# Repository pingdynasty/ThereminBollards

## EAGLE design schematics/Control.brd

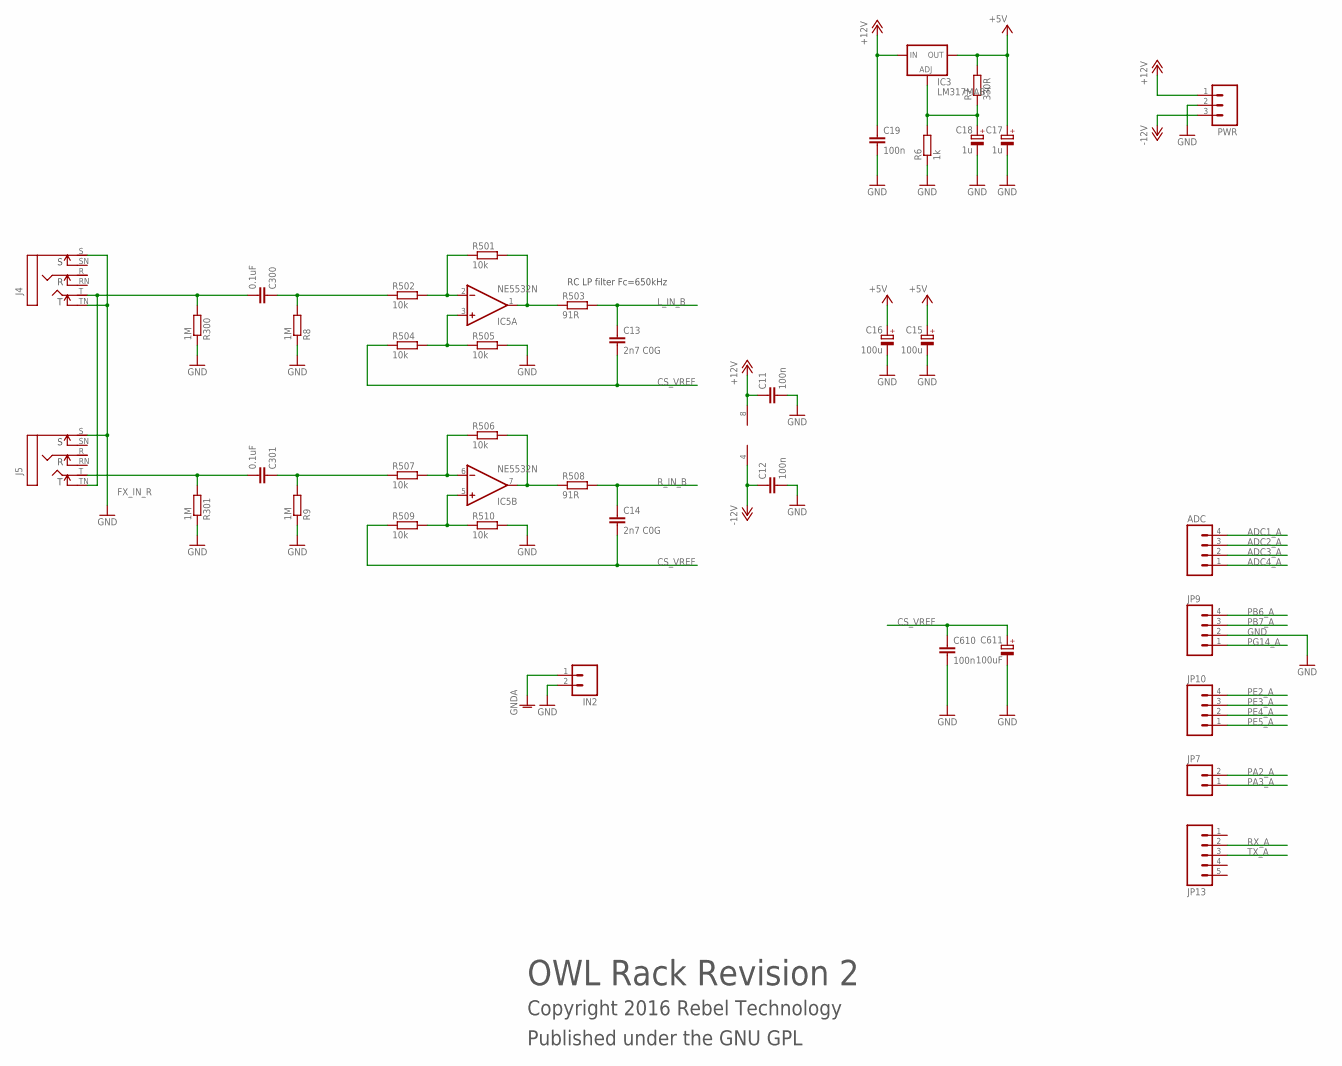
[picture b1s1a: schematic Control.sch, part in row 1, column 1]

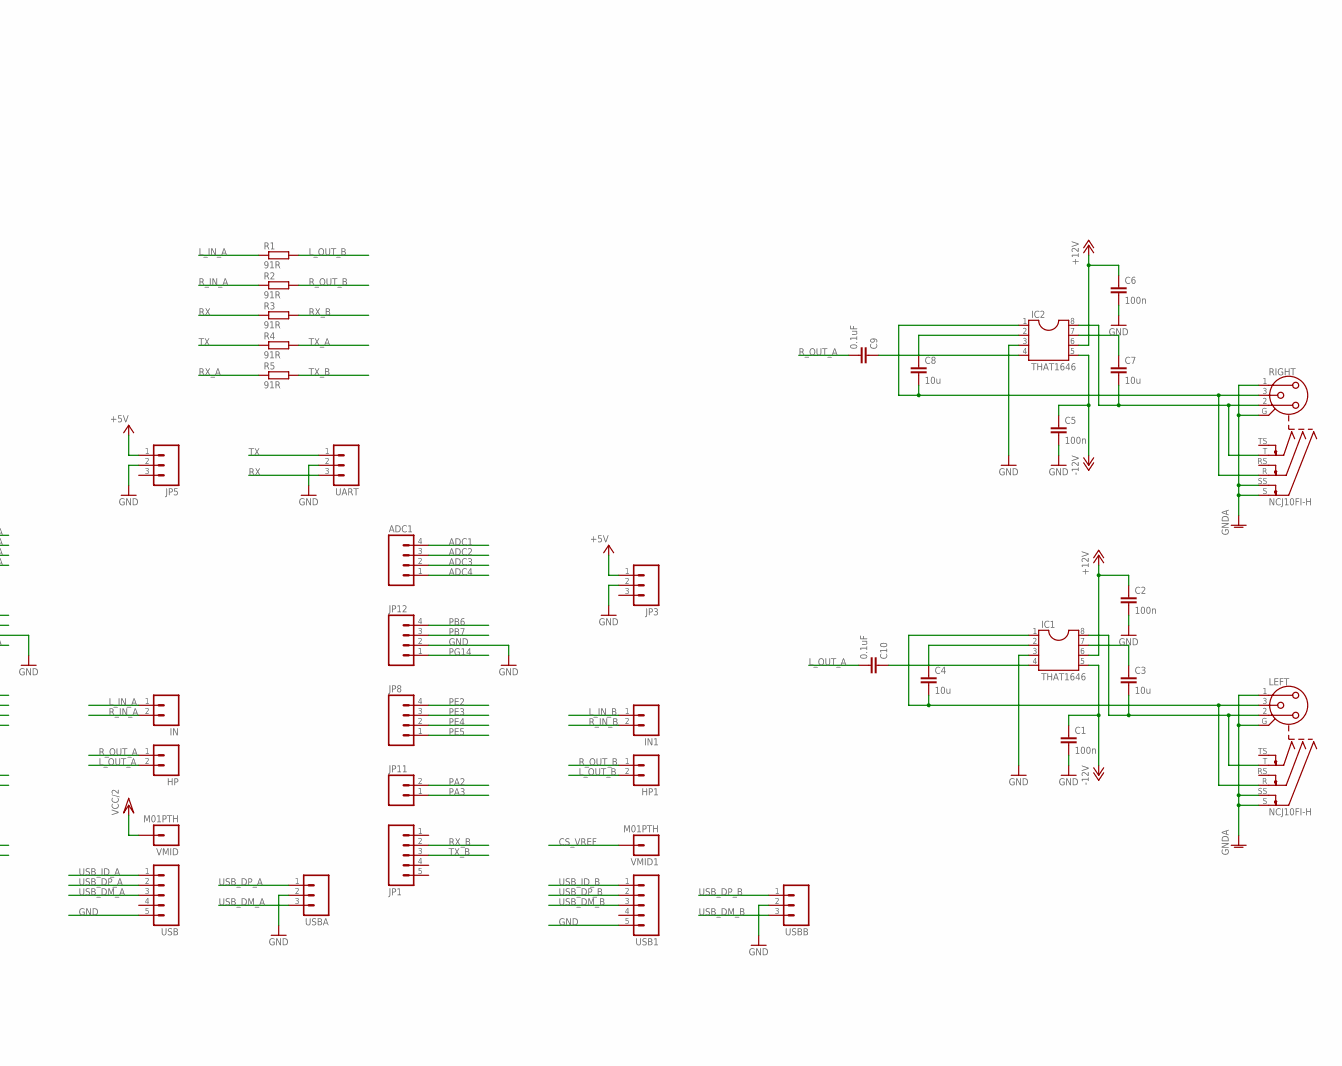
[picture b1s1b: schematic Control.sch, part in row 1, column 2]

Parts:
ADC, ADC1: M04PTH; 1X04
C1, C2, C5, C6, C11, C12, C19, C610: 100n; C050-025X075
C3, C4, C7, C8: 10u; C050-025X075
C9, C10, C300, C301: 0.1uF; C5B3.5
C13, C14: 2n7 C0G; C050-025X075
C15, C16: 100u; E2,5-7
C17, C18: 1u; E2,5-7
C611: 100uF; E2,5-7
HP, HP1: M02PTH; 1X02
IC1, IC2: THAT1646; DIL08
IC3: LM317MABT; TO220L1
IC5: NE5532N; DIL08
IN, IN1, IN2: M02PTH; 1X02
J4, J5: NEUTRIK_NMJ6HCD2; NMJ6HCD2
JP1, JP13: M05PTH; 1X05
JP3, JP5: M03PTH; 1X03
JP7, JP11: M02PTH; 1X02
JP8, JP9, JP10, JP12: M04PTH; 1X04
LEFT: NCJ10FI-H
PWR: M03PTH; 1X03
R1, R2, R3, R4, R5, R503, R508: 91R; 0204/7
R6: 1k; 0204/7
R7: 330R; 0204/7
R8, R9, R300, R301: 1M; 0204/7
R501, R502, R504, R505, R506, R507, R509, R510: 10k; 0204/7
RIGHT: NCJ10FI-H
UART: M03PTH; 1X03
USB, USB1: M05PTH; 1X05
USBA: M03PTH; 1X03
USBB: M03PTH; 1X03
VMID, VMID1: M01PTH; 1X01

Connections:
+5V: C15.+, C16.+, C17.+, IC3.2 (OUT), JP3.1, JP5.1, R7.2
+12V: C2.1, C6.1, C11.1, C19.1, IC1.6, IC2.6, IC3.3 (IN), IC5.8 (V+), PWR.1
-12V: C1.1, C5.1, C12.1, IC1.5, IC2.5, IC5.4 (V-), PWR.3
ADC1: ADC1.4
ADC1_A: ADC.4
ADC2: ADC1.3
ADC2_A: ADC.3
ADC3: ADC1.2
ADC3_A: ADC.2
ADC4: ADC1.1
ADC4_A: ADC.1
CS_VREF: C13.2, C14.2, C610.1, C611.+, R504.1, R509.1, VMID1.1
FX_IN_L: C300.2, J4.T, J5.TN, R300.2
FX_IN_R: C301.2, J5.T, R301.2
GND: C1.2, C2.2, C5.2, C6.2, C11.2, C12.2, C15.-, C16.-, C17.-, C18.-, C19.2, C610.2, C611.-, IC1.3, IC2.3, IN2.2, J4.S, J4.TN, J5.S, JP3.2, JP5.2, JP9.2, JP12.2, PWR.2, R6.1, R8.1, R9.1, R300.1, R301.1, R505.2, R510.2, UART.2, USB.5, USB1.5, USBA.2, USBB.2
GNDA: IN2.1, LEFT.1, LEFT.G, LEFT.S, LEFT.SS, RIGHT.1, RIGHT.G, RIGHT.S, RIGHT.SS
L_IN_A: IN.1, R1.1
L_IN_B: C13.1, IN1.1, R503.2
L_OUT_A: C10.2, HP.2
L_OUT_B: HP1.2, R1.2
unnamed: IC5.7 (OUT), R506.2, R508.1
unnamed: C3.2, IC1.8, LEFT.2, LEFT.T
unnamed: C4.2, IC1.1, LEFT.3, LEFT.R
unnamed: C3.1, IC1.7
unnamed: C4.1, IC1.2
unnamed: C9.1, IC2.4
unnamed: C7.1, IC2.7
unnamed: C10.1, IC1.4
unnamed: C8.1, IC2.2
unnamed: C18.+, IC3.1 (ADJ), R6.2, R7.1
unnamed: C7.2, IC2.8, RIGHT.2, RIGHT.T
unnamed: C8.2, IC2.1, RIGHT.3, RIGHT.R
unnamed: C300.1, R8.2, R502.1
unnamed: C301.1, R9.2, R507.1
unnamed: IC5.3 (+IN), R504.2, R505.1
unnamed: IC5.2 (-IN), R501.1, R502.2
unnamed: IC5.1 (OUT), R501.2, R503.1
unnamed: IC5.5 (+IN), R509.2, R510.1
unnamed: IC5.6 (-IN), R506.1, R507.2
PA2: JP11.2
PA2_A: JP7.2
PA3: JP11.1
PA3_A: JP7.1
PB6: JP12.4
PB6_A: JP9.4
PB7: JP12.3
PB7_A: JP9.3
PE2: JP8.4
PE2_A: JP10.4
PE3: JP8.3
PE3_A: JP10.3
PE4: JP8.2
PE4_A: JP10.2
PE5: JP8.1
PE5_A: JP10.1
PG14: JP12.1
PG14_A: JP9.1
RX: R3.1, UART.3
RX_A: JP13.2, R5.1
RX_B: JP1.2, R3.2
R_IN_A: IN.2, R2.1
R_IN_B: C14.1, IN1.2, R508.2
R_OUT_A: C9.2, HP.1
R_OUT_B: HP1.1, R2.2
TX: R4.1, UART.1
TX_A: JP13.3, R4.2
TX_B: JP1.3, R5.2
USB_DM_A: USB.3, USBA.3
USB_DM_B: USB1.3, USBB.3
USB_DP_A: USB.2, USBA.1
USB_DP_B: USB1.2, USBB.1
USB_ID_A: USB.1
USB_ID_B: USB1.1
VCC/2: VMID.1

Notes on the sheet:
OWL Rack Revision 2
Copyright 2016 Rebel Technology
Published under the GNU GPL
RC LP filter Fc=650kHz

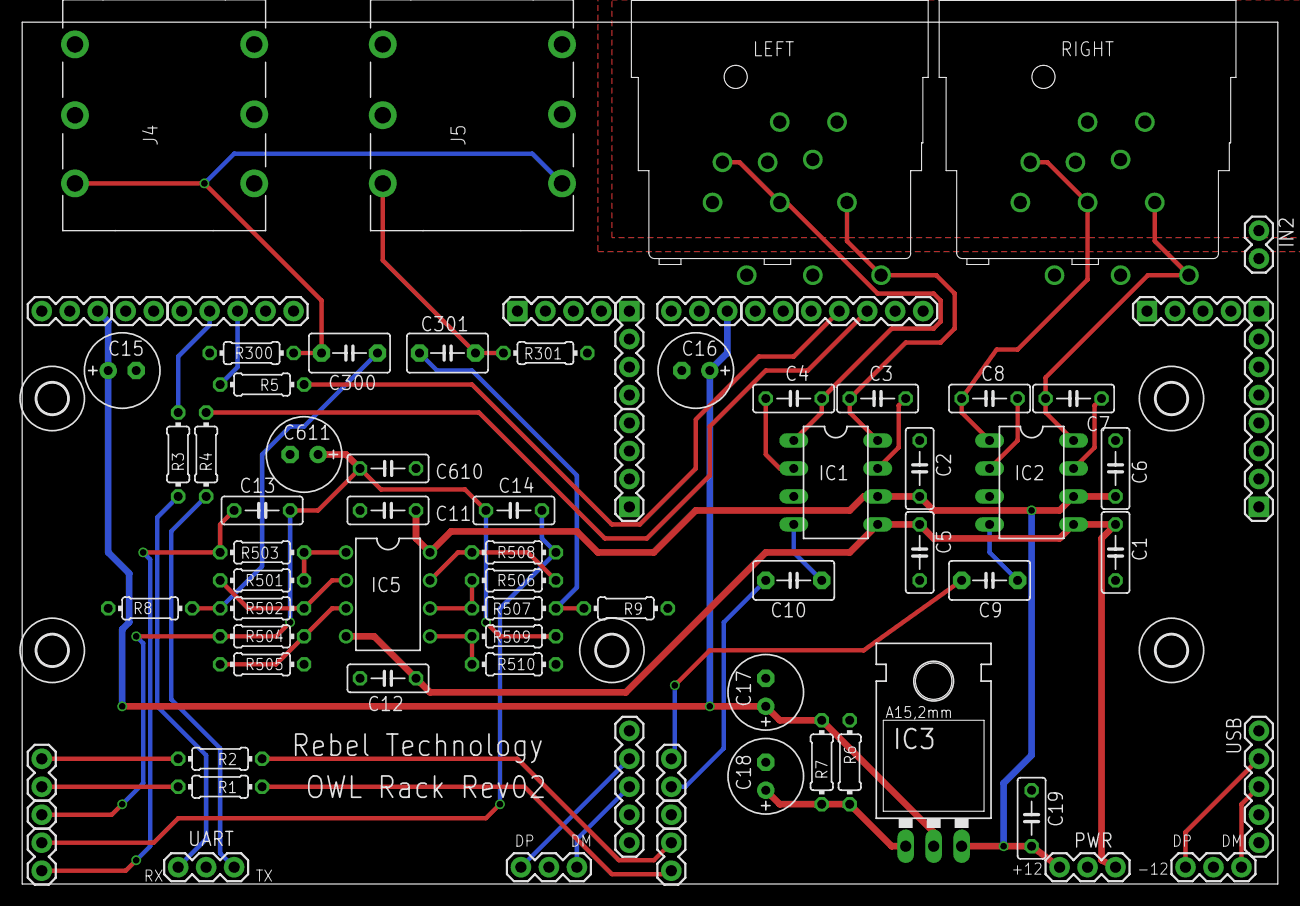
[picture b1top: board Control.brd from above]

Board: 2 copper layers, 114.0 x 78.2 mm, 82 parts (0 on the bottom side), 45 nets.

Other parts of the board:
U$1, U$3, U$4, U$5, U$6: 2,8

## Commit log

2016-05-16 combining designs for rack control board
2016-05-16 rev01 for pcbtrain express fab
2016-07-14 added +5v reg, change power connection, reduced board size
2016-07-14 added usb connections and adjusted audio input circuit
2016-07-14 adjusted labels
2016-07-19 added top polygon
2016-07-20 Drawings for 1URack
    Front and Back Panel ,DXF's,PDF's & Solidworks files
2016-07-20 Changes to FrontPanel Drawing
    Encoder cut-outs rotated 180 degrees and OLED and related encoders moved
    closer to centre
2016-07-22 GCodes of Front and Back Panel
2016-07-22 Tool Dimensions and Drill Path Changed
    Drilling of corners of rectangular cut-outs for relief and less strain
2016-07-22 updated component values
2016-07-27 Changes to Back and Front Panel Cut Outs
2016-08-04 Theremin Bollards logo
2016-08-04 Theremin Bollards Logo Added
2016-08-04 Paddy Mods
2016-08-08 dimensioning updates Paddy
2016-08-09 ThereminBollards Logo
    Solidworks part containing ThereminBollards Logo
2016-08-10 reverted to version without logo
2016-08-10 Theremin Bollard Logo Added to Scale
    SLDPRT and PDF files
2016-08-11 added logo AI

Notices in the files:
parts and their libraries:
SparkFun: Licensing: CC v3.0 Share-Alike You are welcome to use this library for commercial purposes.
